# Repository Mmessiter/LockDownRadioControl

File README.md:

# LockDownRadioControl, Version 1

> [!NOTE]
> **Version 2 is here (October 2026).** The same transmitter with a 5-inch WiFi touchscreen that updates the whole radio from the internet, a new receiver that sets up Rotorflight from your phone, and a free phone app.
> - Code, boards and case: the [LDRC_V2 repository](https://github.com/Mmessiter/LDRC_V2).
> - What it does, and how to build one: [messiter.com/LDRC.html](https://messiter.com/LDRC.html) and [Build one](https://messiter.com/ldrc/build.html).
> - **Starting a new build? Build Version 2.** It uses this same main board, sticks and switches, with a cheaper screen and a new case front, and it updates itself.
>
> This repository is **Version 1**. It still flies, and its radio link is the one Version 2 uses. New work happens in Version 2.

<sub>A Version 1 transmitter with Malcolm's Goblin RAW 420.</sub>

**LockDownRadioControl (LDRC)** is a free, open-source 16-channel radio control system for models of all kinds: a transmitter and a receiver that you build yourself. Malcolm Messiter started it in the lockdown of May 2020. He and his club friends have flown many models with it since.

---

## Why choose LDRC

### (0) Simple to use

LDRC does not try to speak every protocol or offer every option. It does what you need to fly, cleanly and reliably, so it is quick to learn and quick to use. (It still speaks SBUS, PWM and MSP, for flight controllers and servos.)

### (1) The right model loads by itself (AMS)

Switch on a model and the transmitter loads its memory. Most systems only warn you, or stop you, when the wrong memory is loaded. LDRC finds the right one.

### (2) Backups on the transmitter

Back up a model memory to the transmitter's card in one touch, and restore it just as easily. Experiment, and undo it if you need to.

### (3) Send model memories without wires

Copy a model memory to another transmitter over the radio link: no cables, no swapping cards, no computer. The model's ID goes with it, so the other transmitter loads it by itself too. Handy for buddy-box lessons, so instructor and pupil fly the same set-up.

### (4) Wireless buddy box, no extra hardware

Buddy-box with no extra modules or dongles. Hand-over is instant. When the instructor takes over to save the model, there is no hesitation. A "nudge" mode lets the pupil fly while the instructor nudges.

### (5) The link, in full view

The telemetry page shows the packet rate (now and average), lost packets, the longest and average reconnection times, swaps between the receiver's radios, and a chart of how long each reconnection took.

### (6) Rotorflight at the field

If your helicopter runs Rotorflight (a Nexus, or any flight controller with Rotorflight 2.2 or 2.3), you can change PIDs, rates and the governor from the transmitter at the field. No laptop, except for the first set-up.

---

## Introduction

- **16 channels**, for planes, gliders, helicopters and more.
- **Flown since 2020** by Malcolm and his friends.
- **Cost:** Malcolm's 2020 estimate was about £120 for a transmitter. Prices have risen: today the Teensy, the Nextion screen and the sticks alone cost about £135–£155. A receiver is about £35 (prices vary by shop).
- **Transmitter:** a Teensy 4.1 (600 MHz ARM Cortex-M7), an Ebyte ML01DP5 radio, a Nextion NX8048P050 5-inch touchscreen, FrSky M9 Hall-sensor sticks and FrSky X9D Plus trims.
- **Receiver:** a Teensy 4.0 and one or two Ebyte ML01SP4 radios.
- **Cases:** 3D-printed in the plastic you prefer. Malcolm uses PETG.
- **Everything is here:** the code for the transmitter, its screen and the receiver; the Gerbers for the circuit boards; the STL files for the cases; the help texts for the SD card. There is nothing to stop anyone building one.
- **Help:** email Malcolm at [mmessiter@gmail.com](mailto:mmessiter@gmail.com). He will be happy to help.

<sub>A Version 1 transmitter and receiver.</sub>

Along the way:
- **PPM has gone.** Nobody used it any more, and removing it freed memory and pins.
- **Gliders:** a variometer sounds as the model climbs or sinks, to help find thermals.
- **Helicopters:** Malcolm first planned his own stabilisation. Then he found Rotorflight, and added good support for it instead: telemetry, and PIDs, rates and the governor edited from the transmitter, over MSP.

---

## Features

- 16 channels, about 2,000 steps each (whole microseconds, 500 to 2,500), sent in 12-bit slots.
- 4 banks (flight modes), each with its own curves.
- 32 mixes, for inputs or outputs.
- 90 model memories, and as many backups as the card holds.
  <!-- TODO Malcolm: 90 memories: the code (MAXMODELNUMBER 91: the Models page, automatic model selection and the buddy match run 1-90) and MODELS.TXT say 90 (Version 1 and Version 2 alike). Only the Check IDs page (Model_IDs.h) scans 1-89: please check memory 90 shows there. -->
- Three rates ("dual rates", but three).
- 500 packets a second. Fewer while buddy-boxing, because the instructor's transmitter also talks to the pupil's.
- Frequency hopping across 83 channels of the 2.4 GHz band, about 100 hops a second.
- Very small packets: only the channels that changed are sent, so fewer clash with others.
- **Wireless buddy box**, with a "nudge" mode for teaching.
- **AMS:** the right model memory loads by itself when you connect.
- **The pupil's transmitter loads the same model** as the instructor's.
- **Wireless model sharing** between transmitters, with no SD cards removed.
- Telemetry: the model's battery volts. With the receiver's sensors: GPS position, speed, altitude, heading and distance from home, barometric height.
- Spoken messages and other sounds.
- Your own channel names, inputs and outputs.
- 5-point curves for every channel in every bank: straight, smoothed or expo.
- Failsafe.
- 4 top switches you give jobs to (banks, motor, safety, rates, buddy); four more switches or knobs drive channels 5–8.
- Digital trims, subtrim, reverse, servo speed, macros, a motor timer, log files.
- **Receiver:** up to 11 PWM servo outputs, each with its own frame rate and centre; SBUS.
- **Rotorflight** (Nexus and others): head speed, capacity used, flight-pack volts and more on the screen, and PIDs, rates and the governor changed at the field.
- A variometer for gliders.
- Help on every page.

**With Version 2:** a Version 1 receiver binds and flies with a Version 2 transmitter. Rotorflight editing from a Version 2 transmitter needs a Version 2 receiver. A Version 1 transmitter can send its models to a Version 2 over the air (tested), and two Version 2s swap them. To move up, keep your models, main board, sticks and switches; print the Version 2 case front (it holds the new screen), fit the screen, and update the firmware. Keep your Teensy's card. [Build one](https://messiter.com/ldrc/build.html#transmitter)'s Version 1 box has the steps.

<!-- TODO Malcolm: does a Version 1 owner also need the Version 2 case back (TX_BACK12a_V2), or only the front? Until you say, these READMEs and the website say front only. If yes, say "front and back" in all three READMEs and on the website. -->

---

> [!WARNING]
> **Radio rules.** The radio modules that transmit and receive, Ebyte's E01-ML01DP5 (transmitter) and E01-ML01SP4 (receiver), carry the CE mark and FCC ID 2ALPH-E01. They run at about 100 mW (20 dBm), the UK and EU limit for 2.4 GHz; an aerial cannot add power, it only shapes where the signal goes. As with any model you build yourself, check the radio rules where you live before you fly.
>
> LDRC is yours to change: its author often adds a feature within a day of a pilot asking, and everything is open, so you can change it yourself. Commercial systems are almost always take it or leave it. See [how LDRC compares](https://messiter.com/ldrc/transmitter.html#compare).

<!-- TODO Malcolm: please confirm the radio modules' output. Ebyte sells the ML01DP5 (transmitter) and the ML01SP4 as 20 dBm (100 mW); the firmware always sets RF24_PA_MAX (TransmitterCode transceiver.h line 16, ReceiverCode radio.h line 386). -->

## Building a Version 1

**If you are starting now, build Version 2** ([LDRC_V2](https://github.com/Mmessiter/LDRC_V2), [Build one](https://messiter.com/ldrc/build.html)). The steps there cover this main board, the sticks, the switches and the shared case parts.

What is in this repository:

| Folder | What it is |
|---|---|
| `TransmitterCode/` | The transmitter's Teensy 4.1 firmware (PlatformIO, build `teensy41`) |
| `ReceiverCode/` | The receiver's Teensy 4.0 firmware (PlatformIO, build `teensy40`) |
| `HEX_Files/` | Ready-built firmware (`TX.hex`, `RX.hex`) for PJRC's [Teensy Loader](https://www.pjrc.com/teensy/loader.html). `TX.command` and `RX.command` load them on a Mac. They may be older than the source |
| `Nextion files/` | The screen: `TX_NEXTION.HMI`, for the Nextion Editor |
| `TransmitterCode/SD Examples/` | What goes on the Teensy's card (help texts, models, pictures) and on the Nextion's card (pictures) |
| `Help files for SD/` | The help texts, one per page |
| `Circuits/` | The boards as Proteus projects, with Gerbers in the `CADCAM` folders: transmitter, receiver (11 PWM outputs: `RX_11_PWM_MAY2024 - CADCAM.ZIP`) and the receiver's sensor hub |
| `STL files/` | The printed cases (STEP sources in `STL files/STEP files/`) |
| `Noises/` | The sounds |
| `Images/` | Photographs |

**Flash the firmware:** with PlatformIO (`pio run -e teensy41 -t upload` in `TransmitterCode`, `pio run -e teensy40 -t upload` in `ReceiverCode`), or load the ready-built `.hex` files with the Teensy Loader.

**Load the screen:** open `TX_NEXTION.HMI` in the Nextion Editor, compile it, and load it onto the Nextion.

**Before the first flight**, blades off, do every check in [Build one → Testing before the first flight](https://messiter.com/ldrc/build.html#testing): failsafe and range test included.

<!-- TODO Malcolm: (1) The README said "common anode" for the transmitter's RGB LED; the board's netlist and the firmware suit common cathode. Which is right? (2) The INA219 module was missing from the transmitter BOM; the firmware reads the transmitter battery only from it. Confirm. (3) Buddy rate: the code paces model packets at least 4 ms apart (up to 250 a second; a comment says "only 200Hz"); the old README said 200 + 200 = 400. Which figure? (4) How do you load the Nextion: from its microSD slot or over serial? (5) ROADMAP.md in this repo is from May 2026 and describes RXV2 as living here; update or remove it. -->

---

# The LockDownRadioControl protocol

## 1. Overview and addressing

LDRC's radio protocol is its own, and it is open. It is low-latency and built for very high reliability. It is described here because it is the most important part of any control system: it must simply never fail.

### 1.1 Device identification

Each transmitter and receiver is identified by a hardware ID derived from the MAC address of its Teensy 4.x microcontroller. (Version 2 receivers use their ESP32-S3's MAC address the same way.)

### 1.2 Binding

Binding sets up a trusted link between one transmitter and one receiver.

- **Unbound:** a receiver in bind mode listens for a reserved **default pseudo-ID**. A transmitter in bind mode sends with that pseudo-ID.
- **Handshake:** once they connect on the pseudo-ID:
  1. The transmitter sends its unique hardware ID.
  2. The receiver stores the transmitter's ID in non-volatile memory.
  3. The receiver sends its own unique hardware ID in its acknowledgement.
  4. The transmitter checks the receiver's ID, to load the right model memory.
- **Bound:** from then on, every packet uses the transmitter's unique ID as the pipe address. A receiver that is not in bind mode ignores everything except packets with its stored transmitter ID.

## 2. Physical layer and link control

### 2.1 Frequency hopping (FHSS)

The receiver drives the frequency hopping, in the 2.4 GHz ISM band.

- **Frequency tables:** both ends keep two tables in step:
  - **Main table:** 83 legal frequencies.
  - **Discovery table:** 3 of them, used to connect quickly.
- **Hopping:** the sequence is pseudo-random. The receiver names the *next* frequency in its acknowledgement (section 3.2).
- **Hop timing:** about 100 hops a second. The order to hop is the top bit of the acknowledgement's first byte.

### 2.2 Connecting and reconnecting

- **Discovery:** at start-up, or after losing the signal, both ends cycle through the discovery table, to lock on quickly.
- **Active:** once locked, both switch at once to the main table.
- **Failsafe:** if the link is lost and not found again within the time-out, the receiver goes to failsafe and the transmitter goes back to searching.

## 3. Packets

### 3.1 Downlink (transmitter to receiver)

Packets vary in length, to save air time. About 500 are sent a second, at 250 kbit/s.

**A. Control packets.** These carry the channels, and come first.

- **Header (16 bits):** one bit per channel.
  - Bit *N* set (1): channel *N* has changed, or is due to be repeated.
  - Bit *N* clear (0): channel *N* has not changed.
- **Payload:** the changed channels follow, packed in 12-bit slots.
- **Receiving:** the receiver reads the length (more than 2 bytes) and the header, unpacks the data and puts it on the right outputs.

**B. Configuration packets.** These carry settings. They are slipped in between control packets, so control is never held up.

- **Marker:** a zero header (`0x0000`) followed by a payload.
- **Contents:** the payload's first 12 bits name the parameter (4,096 possible).
- **Size:** up to 12 words of data a packet. Only the low 12 bits of each word are used, because of the packing.

### 3.2 Uplink (receiver to transmitter)

The receiver sends an acknowledgement (ACK) payload for every packet it receives. It is always 6 bytes.

| Byte | Bits | What it holds |
| :--- | :--- | :--- |
| **0** | 7 (top bit) | **Hop flag:** 1 = hop, 0 = stay |
| **0** | 0–6 | **Data type:** what bytes 1–4 hold |
| **1–4** | all | **Telemetry or other data**, as the data type says |
| **5** | all | **Next frequency:** its place in the pseudo-random table |

## 4. Errors and latency

- **One retry only.** If a packet is lost, the radio tries again exactly once. Then it moves on, so new stick positions always win over old ones. There is never a backlog of stale data.
- **Air time:** large configuration transfers are slipped between control packets, so the controls keep most of the air time.

## 5. Wireless buddy box

The instructor's (master) transmitter takes turns between the model and the pupil's (buddy) transmitter.

- **Turns:**
  - Master → model: packets at least 4 ms apart.
  - Master → buddy: one packet between each pair of model packets.
- **Air rates:** master ↔ model 250 kbit/s; master ↔ buddy 2 Mbit/s.
- **How it works:**
  1. Between control packets to the model, the master sends a packet to the buddy.
  2. The buddy answers with its stick positions in its acknowledgement.
  3. The master mixes or swaps the controls, by its own switch, before it sends to the model.
- **No clashes:** the buddy link uses the same frequency table, but walks it in the **opposite direction**.
- **Same model:** the master's packets to the buddy carry the model's ID. The buddy checks it, or loads the right model memory by itself.

---

# Bill of Materials (BOM)

## Receiver (Version 1)

| Category | Item | Details | Qty |
| --- | --- | --- | --- |
| Structural | PETG filament or similar | For the case | – |
| Structural | IPEX dipole aerial | 2.4 GHz | 2 |
| Connectors | Male headers | Various | Several |
| Connectors | 3-row male headers | – | Some |
| Materials | Solder | – | Some |
| PCB and modules | Printed circuit board | From the Gerbers | 1 |
| PCB and modules | Teensy 4.0 | Main microcontroller | 1 |
| PCB and modules | Ebyte ML01SP4 | Radio module | 2 |
| Power | AMS1117 3.3 V regulator | Linear regulator | 1 |
| Power | Pololu S9V11F5 regulator | Better than a 7805, same pins | 1 |
| Passive components | Tantalum capacitor | 47 µF, 1206 SMD | 2 |
| Passive components | Ceramic capacitor | 100 nF, 1206 SMD | 2 |
| Passive components | LED | 1206 SMD, any colour | 1 |
| Passive components | Resistor | 100 Ω, 1206 SMD, for the LED | 1 |
| Passive components | Tantalum capacitor | 330 µF, 0E907, SMD | 1 |

## Transmitter (Version 1)

| Category | Item | Details | Qty |
| --- | --- | --- | --- |
| Structural | PETG filament or similar | For the case | – |
| Structural | RGB LED | 5 mm (the board and firmware suit common cathode) | 1 |
| Structural | Push button | 16 mm vandal-resistant, momentary SPST | 1 |
| Structural | FrSky trim switches | X9D Plus spare part | 4 |
| Structural | FrSky M9 gimbal | Hall sensor | 2 |
| Structural | Aerial | RP-SMA 2.4 GHz | 1 |
| Structural | Extension cable | RP-SMA male to female, 20 cm | 1 |
| Structural | Self-tapping screws | 3 mm × 2 mm flange, various sizes | Several |
| Structural | M3 bolts with lock-nuts | – | Some |
| Structural | Cable ties | 2 mm wide | Some |
| Structural | Epoxy adhesive | 5-minute | – |
| Structural | Solder | – | Some |
| PCB and modules | Printed circuit board | From the Gerbers | 1 |
| PCB and modules | Teensy 4.1 | Main microcontroller | 1 |
| PCB and modules | Nextion display | NX8048P050, 5-inch capacitive touch | 1 |
| PCB and modules | ML01DP5 | Radio module | 1 |
| PCB and modules | Pololu 2808 | Electronic power switch | 1 |
| PCB and modules | INA219 module | I²C; reads the transmitter's battery | 1 |
| PCB and modules | microSD card | Up to 2 TB, exFAT | 1 |
| PCB and modules | RTC module | I²C, DS1307 | 1 |
| Power | Voltage regulator | Pololu 5 V 1 A S13V10F5, or a 7805 | 2 |
| Power | AMS1117 3.3 V regulator | – | 1 |
| Power | Micro-USB charger | 2S balance | 1 |
| Power | LiPo battery | 2S, a suitable size | 1 |
| Power | Diodes | 1N5406 | 2 |
| Power | Diodes | 1N4001 | 2 |
| Passive components | Electrolytic capacitor | 330 µF | 1 |
| Passive components | Electrolytic capacitor | 100 µF | 1 |
| Passive components | Tantalum capacitor | 330 µF, 0E907, SMD | 2 |
| Passive components | Ceramic capacitor | 330 nF, 1206 SMD | 2 |
| Passive components | Tantalum capacitor | 47 µF, 1206 SMD | 2 |
| Passive components | Ceramic capacitor | 100 nF, 1206 SMD | 4 |
| Passive components | Ceramic capacitor | 10 µF, 1206 SMD | 1 |
| Connectors | Male headers | Various | Several |
| Connectors | Female headers | Various | Several |
| Connectors | 3-row male headers | – | Some |
| Connectors | 2 × 4 socket header | Female | 1 |
| Connectors | Servo cable | Three-core | Some |
| Connectors | DuPont connectors | 3- and 4-pin female | Several |
| Controls | RC switches | Three-position | 8 |
| Controls | Knobs (potentiometers) | Optional: up to 4 can replace switches | Up to 4 |

## Licence

Free software under **GPL-2.0-or-later**: see [LICENSE](LICENSE) and [LICENSING.md](LICENSING.md). Use it, change it, share it. Changed versions must be shared under the same terms.

Copyright (C) 2020–2026 Malcolm Messiter. Since 2025, with Claude (Anthropic's AI) as pair programmer.

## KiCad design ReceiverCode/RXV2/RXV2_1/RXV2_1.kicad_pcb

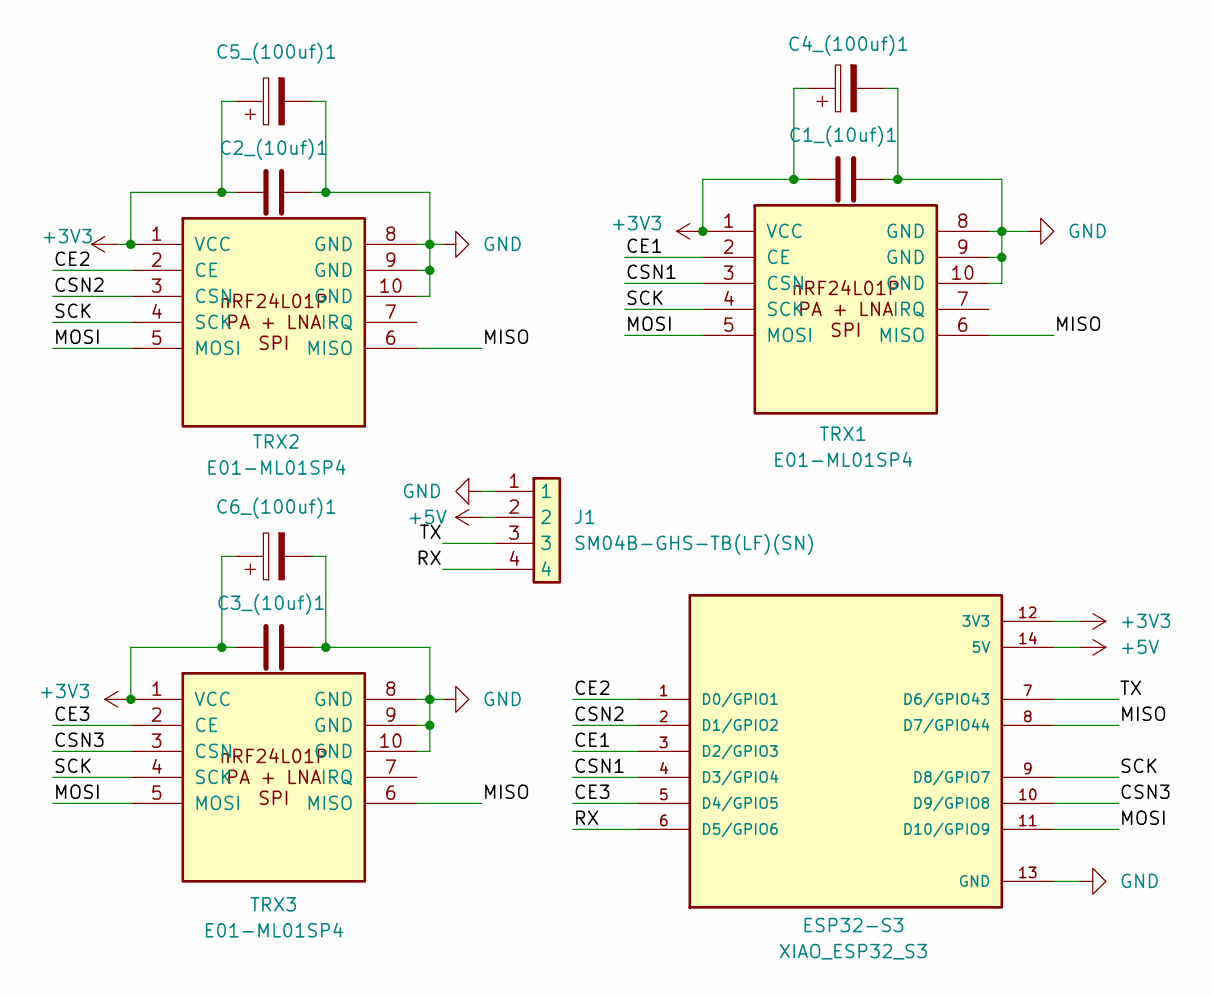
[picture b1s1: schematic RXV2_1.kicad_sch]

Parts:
C1_(10uf)1, C2_(10uf)1, C3_(10uf)1: C; C_0805_2012Metric
C4_(100uf)1, C5_(100uf)1, C6_(100uf)1: C_Polarized; C_1206_3216Metric
ESP32-S3: XIAO_ESP32_S3; XIAO-ESP32-S3-SMD; PARTREV April 22nd, 2026
J1: SM04B-GHS-TB(LF)(SN); JST_GH_SM04B-GHS-TB_1x04-1MP_P1.25mm_Horizontal; MPN SM04B-GHS-TB(LF)(SN)
TRX1, TRX2, TRX3: E01-ML01SP4; EBYTE_E01-ML01SP4_14.5x18mm_SMD

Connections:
+3V3: C1_(10uf)1.1, C2_(10uf)1.1, C3_(10uf)1.1, C4_(100uf)1.1, C5_(100uf)1.1, C6_(100uf)1.1, ESP32-S3.12 (3V3), TRX1.1 (VCC), TRX2.1 (VCC), TRX3.1 (VCC)
+5V: ESP32-S3.14 (5V), J1.2
/CE1: ESP32-S3.3 (D2/GPIO3), TRX1.2 (CE)
/CE2: ESP32-S3.1 (D0/GPIO1), TRX2.2 (CE)
/CE3: ESP32-S3.5 (D4/GPIO5), TRX3.2 (CE)
/CSN1: ESP32-S3.4 (D3/GPIO4), TRX1.3 (CSN)
/CSN2: ESP32-S3.2 (D1/GPIO2), TRX2.3 (CSN)
/CSN3: ESP32-S3.10 (D9/GPIO8), TRX3.3 (CSN)
/MISO: ESP32-S3.8 (D7/GPIO44), TRX1.6 (MISO), TRX2.6 (MISO), TRX3.6 (MISO)
/MOSI: ESP32-S3.11 (D10/GPIO9), TRX1.5 (MOSI), TRX2.5 (MOSI), TRX3.5 (MOSI)
/RX: ESP32-S3.6 (D5/GPIO6), J1.4
/SCK: ESP32-S3.9 (D8/GPIO7), TRX1.4 (SCK), TRX2.4 (SCK), TRX3.4 (SCK)
/TX: ESP32-S3.7 (D6/GPIO43), J1.3
GND: C1_(10uf)1.2, C2_(10uf)1.2, C3_(10uf)1.2, C4_(100uf)1.2, C5_(100uf)1.2, C6_(100uf)1.2, ESP32-S3.13 (GND), J1.1, TRX1.8 (GND), TRX1.9 (GND), TRX1.10 (GND), TRX2.8 (GND), TRX2.9 (GND), TRX2.10 (GND), TRX3.8 (GND), TRX3.9 (GND), TRX3.10 (GND)

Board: 2 copper layers, 11 parts (7 on the bottom side), 14 nets, no tracks yet.

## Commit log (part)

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2026-01-05 update to version number
2026-01-05 bug fix
2026-01-09 update to UI for Rotorflight implementation
2026-01-14 PID Advanced is DONE!
2026-01-15 Bug fix :-)
2026-01-15 new help files ...
2026-01-17 Range checking added
2026-01-17 more range checking added ...
2026-01-18 update - SAVE & RESTORE RF PIDS etc started ...
2026-01-24 Bug Fixed
2026-01-25 update - BOOST added
2026-01-27 bug fix and PID refined
2026-01-27 update - optimisations
2026-01-28 update - HSI offsets added
2026-01-28 update to RX code
2026-01-28 update to timeouts
2026-01-29 update to UI
2026-02-02 updates to UI
2026-02-11 Images can now be selected per model!
2026-02-14 Update - all working well now!
2026-02-15 Safety switch now controls Rotorflight arming if needed.
2026-02-15 update to reduce screen updates
2026-02-15 update - hide AMS sign when connected
2026-02-15 images update
2026-02-18 update: Rates optionally linked to Banks
2026-02-22 Bug fix - Arming channel
2026-02-23 update - Arming channel display
2026-02-23 UPdate to. step files
2026-02-23 optimisations ...
2026-02-24 Update to Rotorflight params save and restore
2026-02-26 Tiny Bug fix - in RotorFlight 'Rates' editing.
    To avoid occasional corruption of data, telemetry is now inhibited briefly while new values are written to EEPROM.
2026-02-27 Bug fix - binding
2026-02-27 update to comments
2026-02-28 MSP port auto-detection added (Serial6, or Serial1)
2026-03-02 new photo
2026-03-07 added HEX files
2026-03-14 update SD examples
2026-03-15 update - bug fix
2026-03-21 bug fix -- log files display
2026-03-21 update hex files
2026-03-29 Tiny bug fix
2026-03-30 update - Governor ...
2026-04-03 update
    update
2026-04-07 update GOVERNOR ready!!
2026-04-13 update
    Global governor setting can now also be saved and restored to SD card in the TX!
2026-04-13 update to HEX files
2026-04-13 update Bank and Rates change no longer via MSP command to Rotorflight
    Bank and Rates change no longer via MSP command to Rotorflight
2026-04-16 Binding bug fixed!
    ... it only affected Rotorflight.
    It's fixed now!
2026-04-17 trivial update
2026-04-18 update (cosmetic)
2026-04-18 update (Hex files)
2026-04-19 help file updates
2026-04-26 update - new Bind button
2026-04-27 update - to User Interface.
2026-05-21 V2 begins ...
2026-05-29 RXV2: model-name UX, help-everywhere, silent-unbound fix, OTA catch-up
    Firmware (v0.9.55 → v0.9.66):
    - Triple-transceiver SPI fix: park CSN HIGH + CE LOW on all three
    slots at boot so present-but-inactive radios don't drive the bus.
    - Radio swap timing tightened to 50 ms (was 200 ms).
    - Silent-while-unbound: V2 keeps autoACK off and ack-payload FIFO
    empty on the default pipe; tryBind() re-enables both the moment a
